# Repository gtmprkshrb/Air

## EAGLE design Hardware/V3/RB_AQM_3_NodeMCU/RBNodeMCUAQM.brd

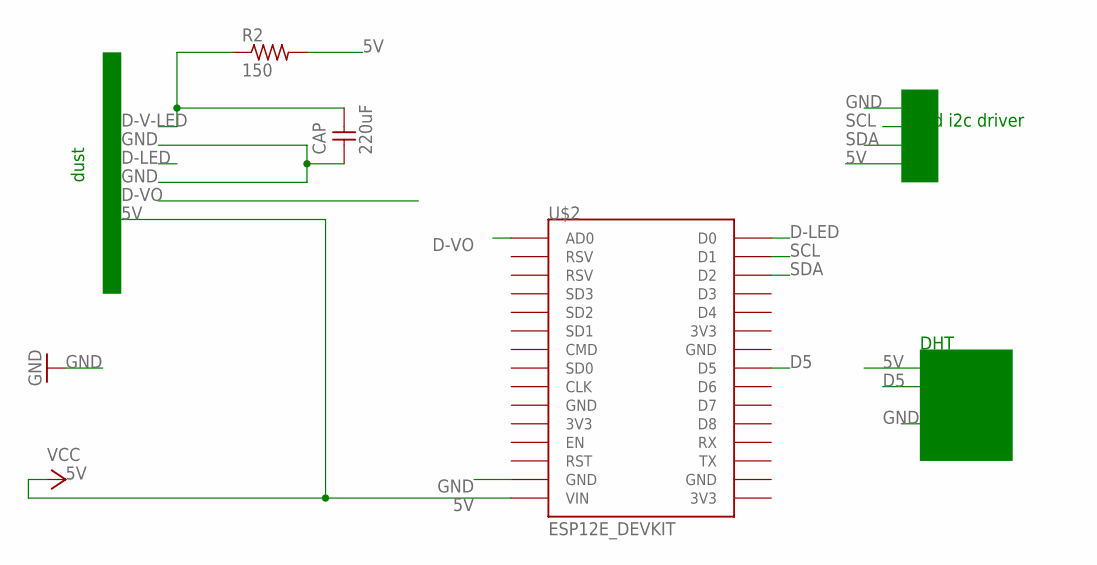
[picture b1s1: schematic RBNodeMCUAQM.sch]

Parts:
CAP: 220uF; C1206FAB
R2: 150; R1206FAB
U$2: ESP12E_DEVKIT

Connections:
5V: R2.2, U$2.VIN
D5: U$2.D5
D-LED: U$2.D0
D-V-LED: CAP.2, R2.1
D-VO: U$2.AD0
GND: CAP.1, U$2.GND@1 (GND)
SCL: U$2.D1
SDA: U$2.D2

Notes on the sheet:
dust
lcd i2c driver
DHT

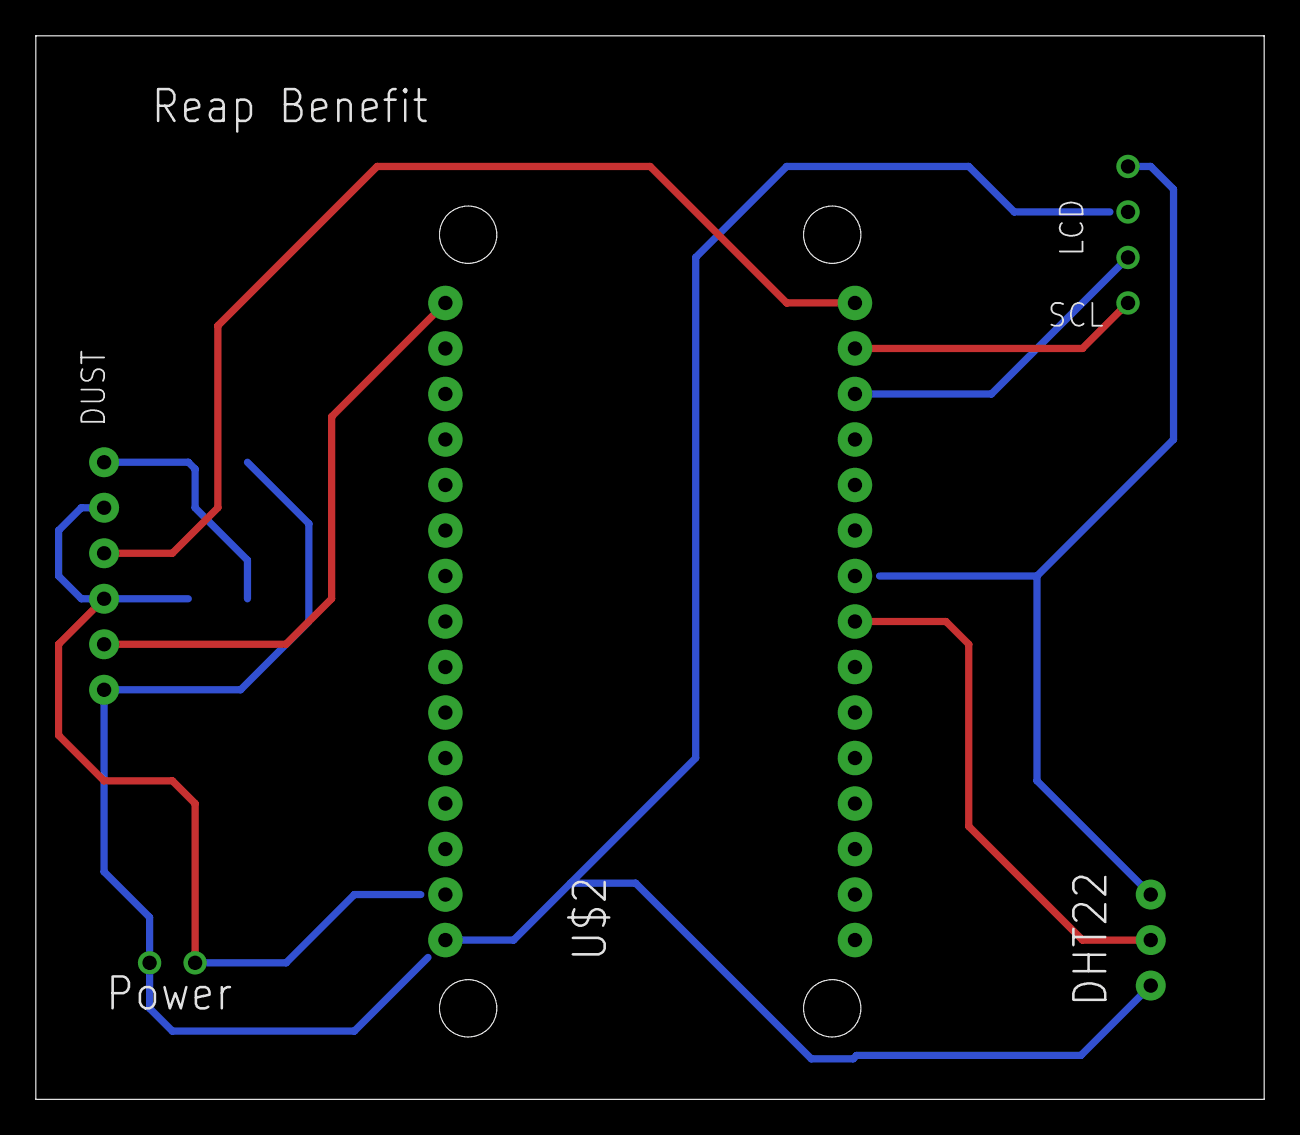
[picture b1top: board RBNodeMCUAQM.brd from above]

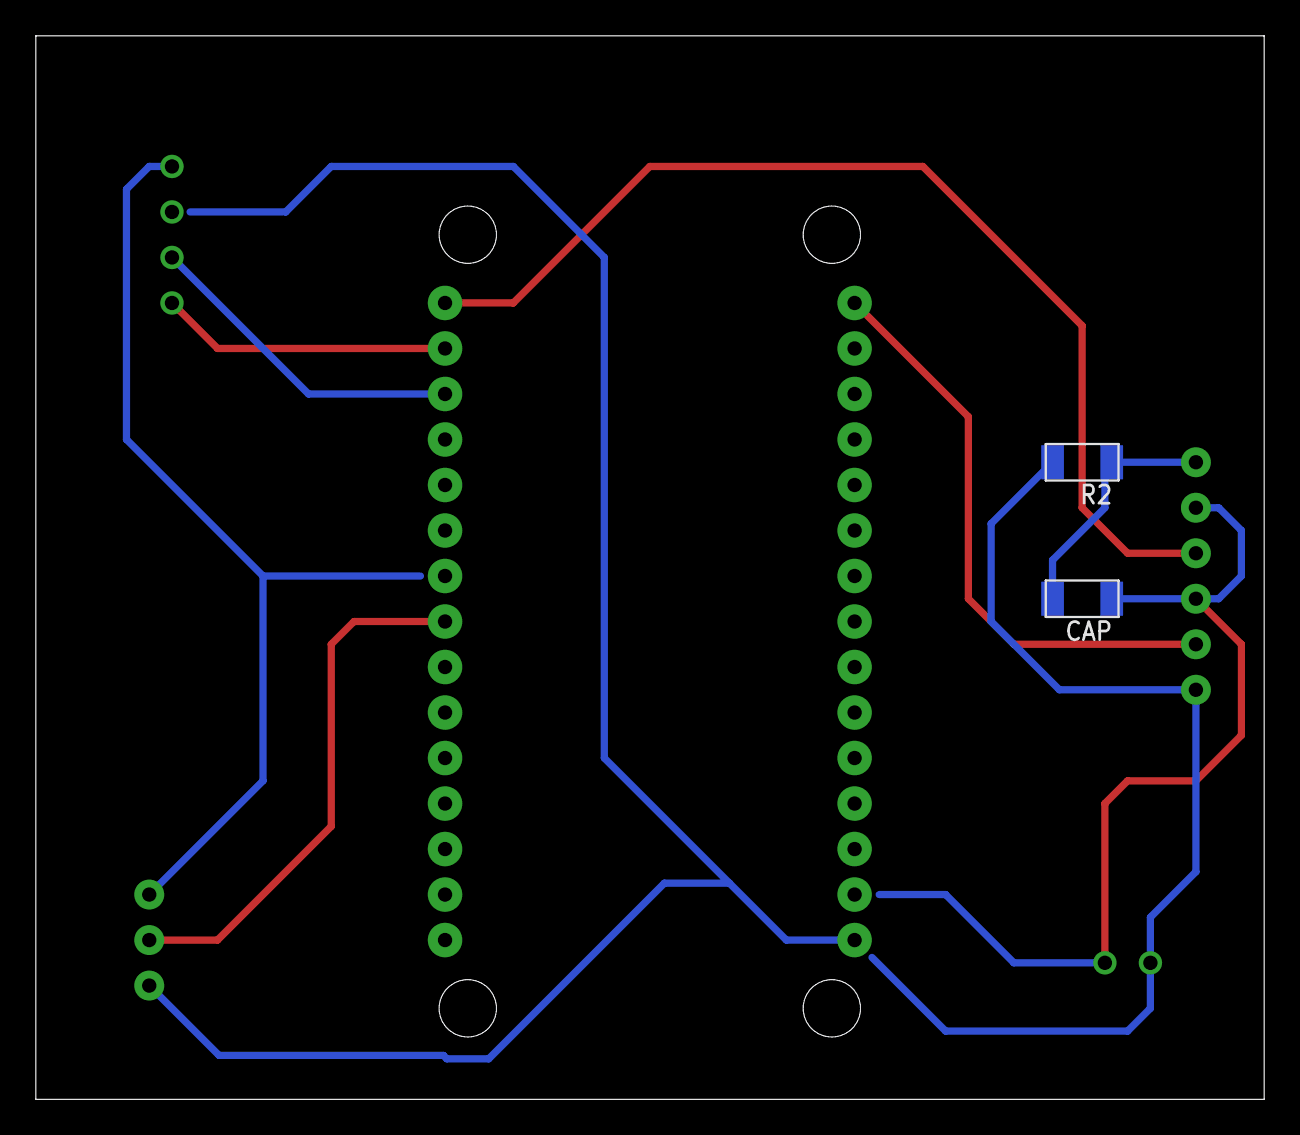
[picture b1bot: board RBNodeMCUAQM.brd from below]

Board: 2 copper layers, 68.6 x 59.4 mm, 3 parts (2 on the bottom side), 3 nets.

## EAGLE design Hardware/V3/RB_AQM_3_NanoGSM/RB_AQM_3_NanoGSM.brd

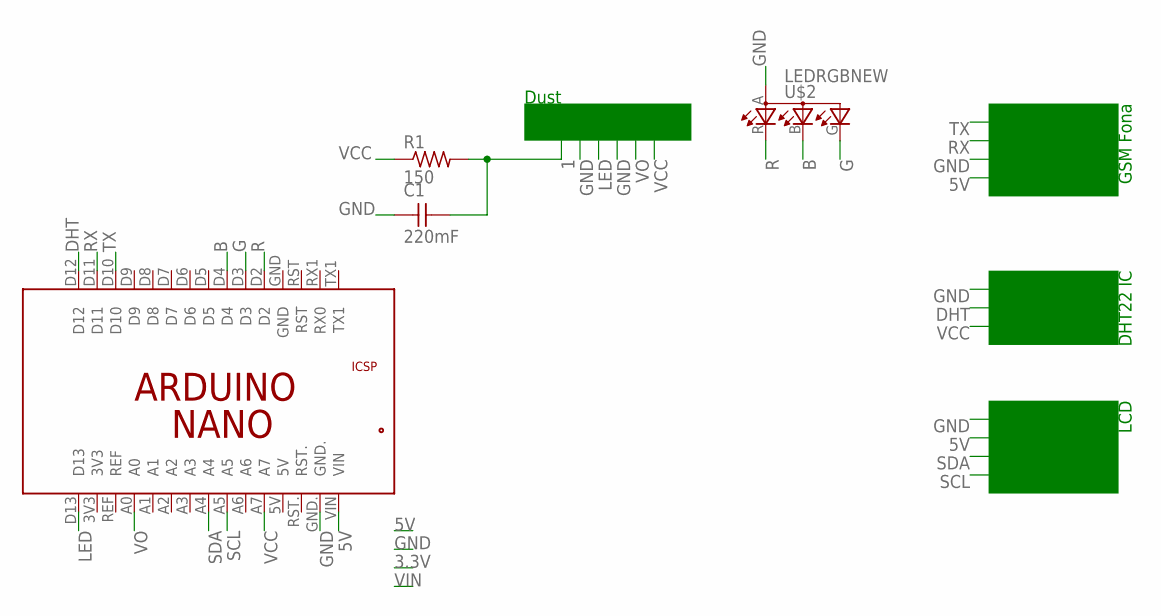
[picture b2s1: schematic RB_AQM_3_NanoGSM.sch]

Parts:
C1: 220mF; C1206FAB
R1: 150; R1206FAB
U$2: LEDRGBNEW; P-LCC-4
U$3: ARD_NANO

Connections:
1: C1.2, R1.2
5V: U$3.VIN
B: U$2.B (CBLUE), U$3.D4
DHT: U$3.D12
G: U$2.G (CGREEN), U$3.D3
GND: C1.1, U$2.A (A2), U$3.GND.
LED: U$3.D13
R: U$2.R (CRED), U$3.D2
RX: U$3.D11
SCL: U$3.A5
SDA: U$3.A4
TX: U$3.D10
VCC: R1.1, U$3.A7
VO: U$3.A0

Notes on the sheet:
DHT22 IC
LCD
GSM Fona
Dust

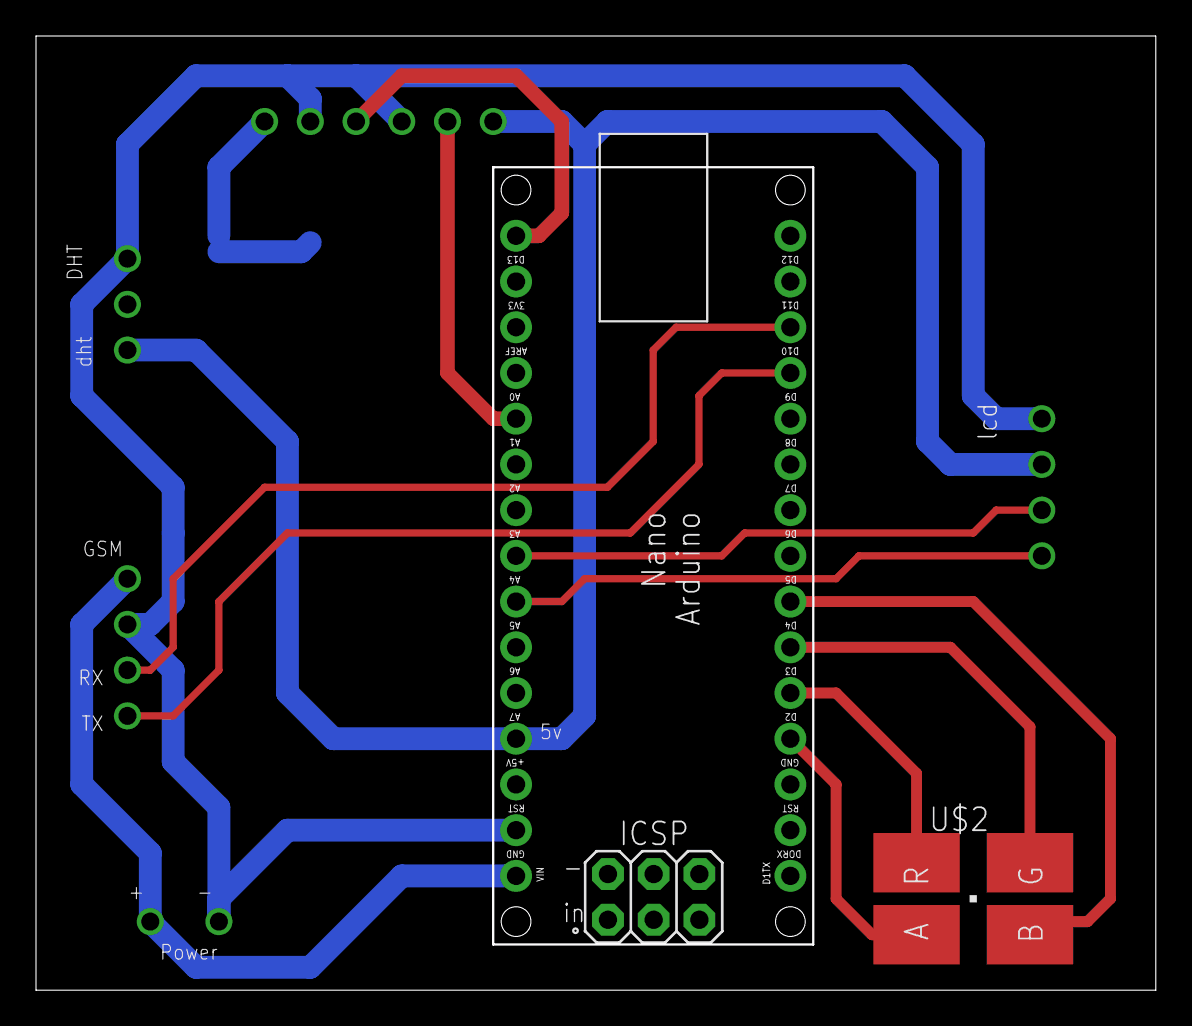
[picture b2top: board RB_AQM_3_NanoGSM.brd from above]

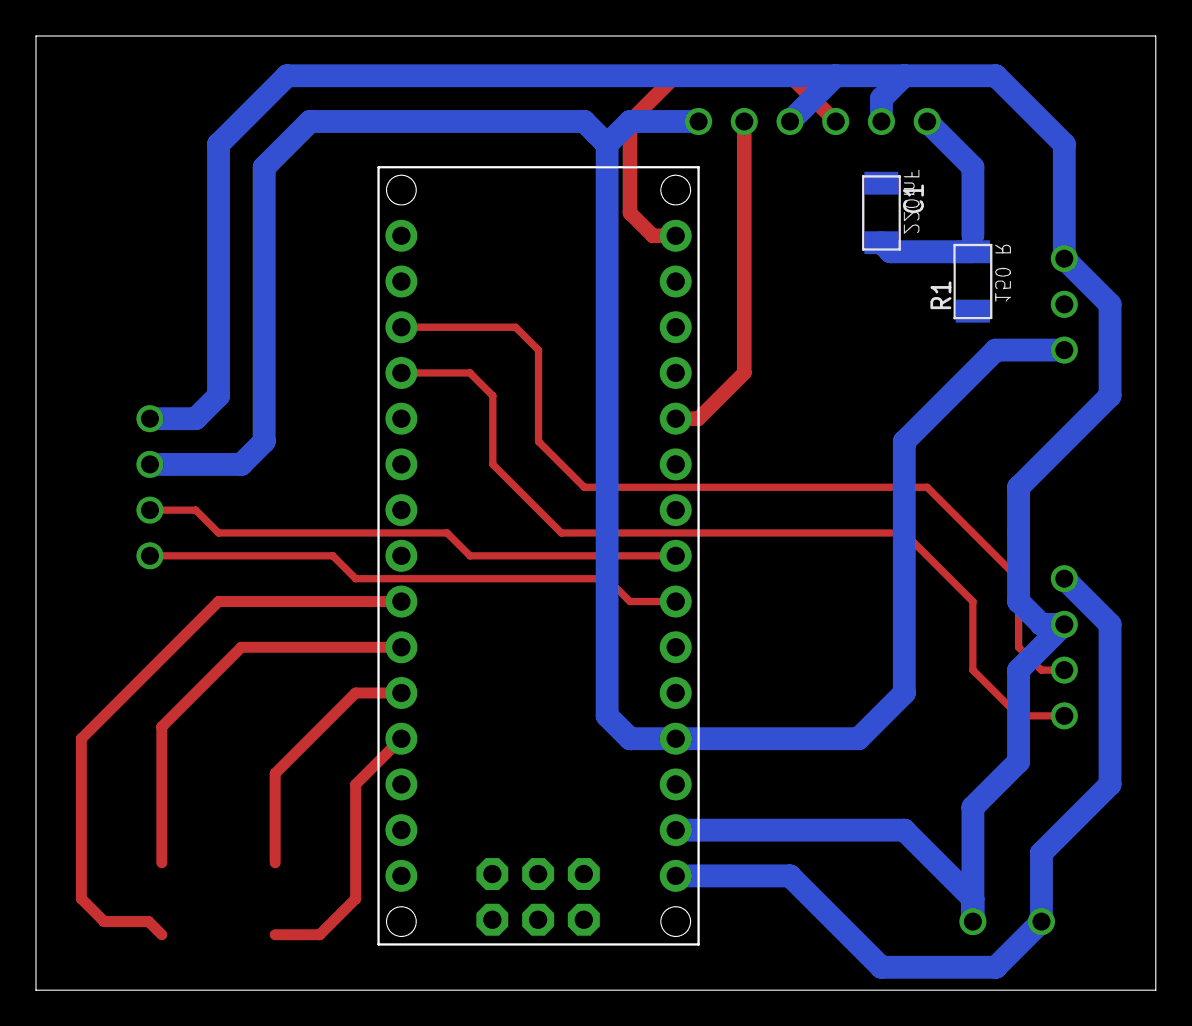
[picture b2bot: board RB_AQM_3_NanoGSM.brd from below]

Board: 2 copper layers, 62.1 x 52.9 mm, 4 parts (2 on the bottom side), 6 nets.

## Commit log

2017-01-16 :boom::camel: Added .gitattributes
2017-03-28 First Upload - Nano with GSM (SMS or GPRS) for DHT22 and Dust and LCD
2017-03-28 Hardware files - schematics and gerber files for the AQM (GSM and WiFi) v3
2017-03-28 Wifi Aqm Code added
2017-05-16 Add files via upload
    Library for the DHT sensor
2017-05-16 Add files via upload
    Library for WiFi chip on NodeMCU
2017-05-16 Add files via upload
    Library for LCD panel to work
